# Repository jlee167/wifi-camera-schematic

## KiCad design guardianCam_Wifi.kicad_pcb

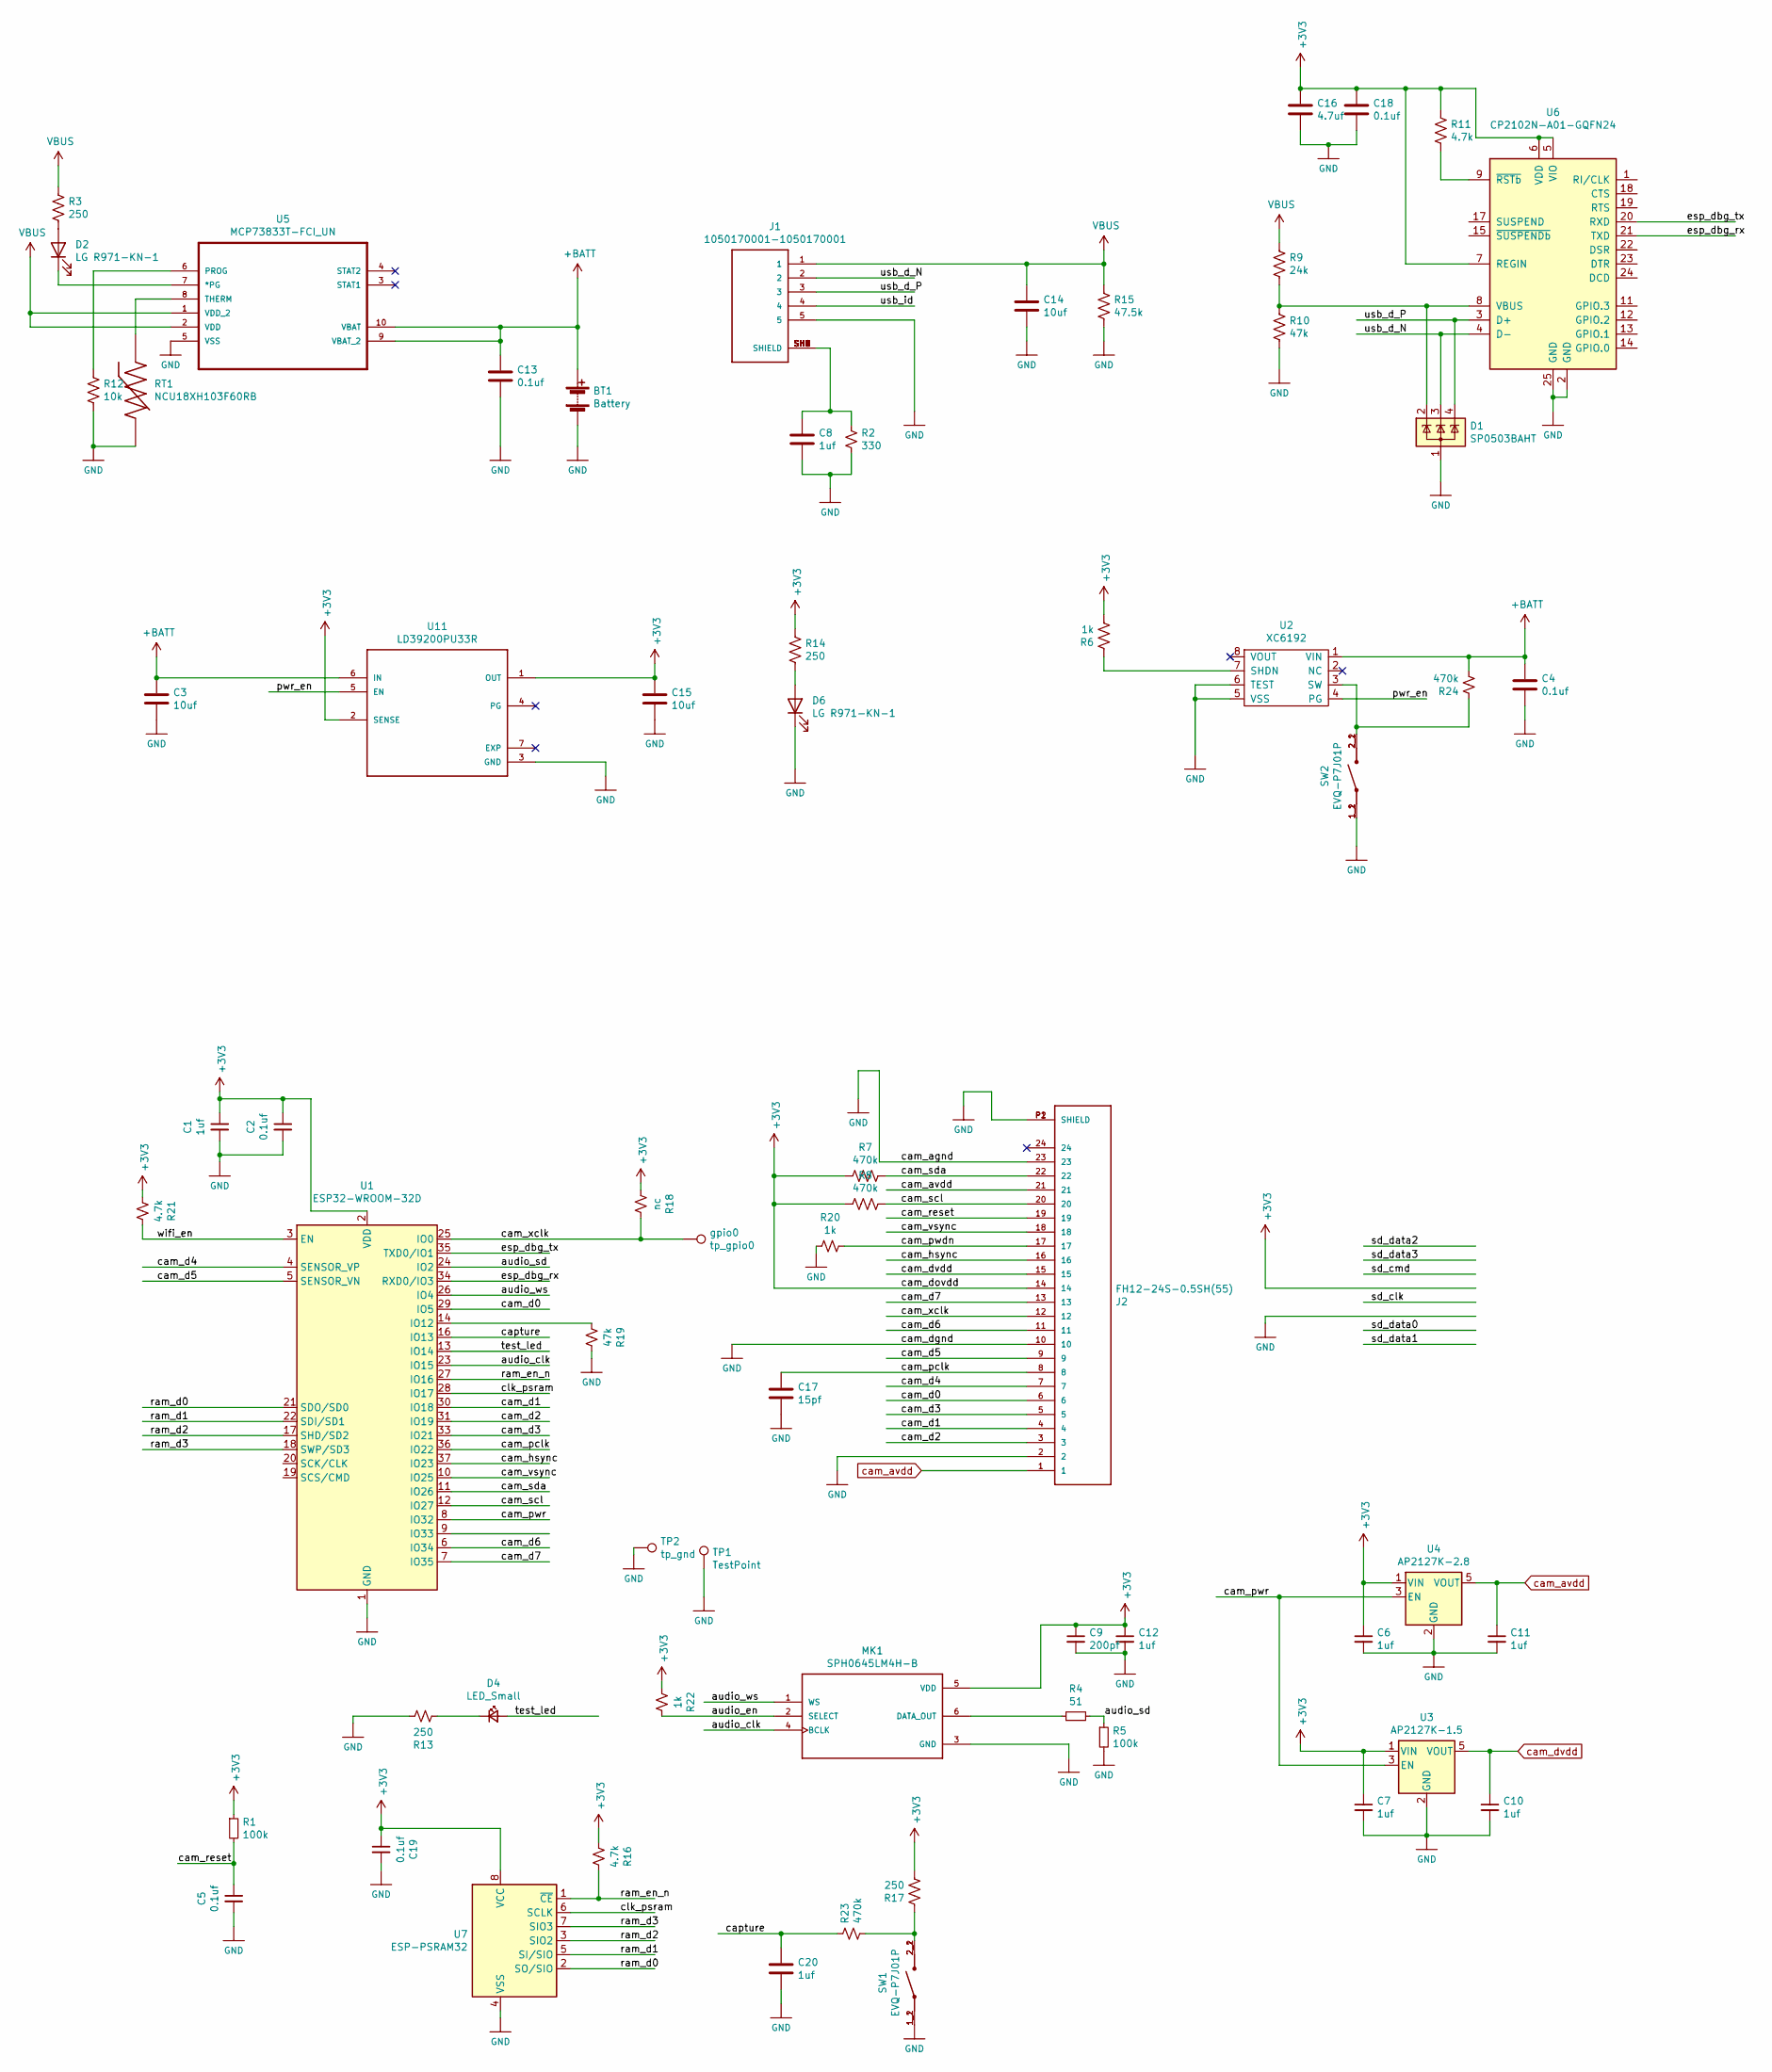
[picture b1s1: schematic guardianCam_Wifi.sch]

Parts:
BT1: Battery; JST_PH_S2B-PH-K_1x02_P2.00mm_Horizontal
C1, C6, C7, C8, C10, C11, C12, C20: 1uf; C_0603_1608Metric_Pad1.05x0.95mm_HandSolder
C2, C4, C5, C13, C18, C19: 0.1uf; C_0603_1608Metric_Pad1.05x0.95mm_HandSolder
C3, C14, C15: 10uf; C_0603_1608Metric_Pad1.05x0.95mm_HandSolder
C9: 200pf; C_0603_1608Metric_Pad1.05x0.95mm_HandSolder
C16: 4.7uf; C_0603_1608Metric_Pad1.05x0.95mm_HandSolder
C17: 15pf; C_0603_1608Metric_Pad1.05x0.95mm_HandSolder
D1: SP0503BAHT; SOT-143
D2, D6: LG R971-KN-1; LED_1206_3216Metric
D4: LED_Small; LED_1206_3216Metric
J1: 1050170001-1050170001; MOLEX_1050170001
J2: FH12-24S-0.5SH(55); HRS_FH12-24S-0.5SH(55)
MK1: SPH0645LM4H-B; MIC_SPH0645LM4H-B
R1, R5: 100k; R_0603_1608Metric_Pad1.05x0.95mm_HandSolder
R2: 330; R_0603_1608Metric_Pad1.05x0.95mm_HandSolder
R3, R13, R14, R17: 250; R_0603_1608Metric_Pad1.05x0.95mm_HandSolder
R4: 51; R_0603_1608Metric_Pad1.05x0.95mm_HandSolder
R6, R20, R22: 1k; R_0603_1608Metric_Pad1.05x0.95mm_HandSolder
R7, R8, R23, R24: 470k; R_0603_1608Metric_Pad1.05x0.95mm_HandSolder
R9: 24k; R_0603_1608Metric_Pad1.05x0.95mm_HandSolder
R10, R19: 47k; R_0603_1608Metric_Pad1.05x0.95mm_HandSolder
R11, R16, R21: 4.7k; R_0603_1608Metric_Pad1.05x0.95mm_HandSolder
R12: 10k; R_0603_1608Metric_Pad1.05x0.95mm_HandSolder
R15: 47.5k; R_0603_1608Metric_Pad1.05x0.95mm_HandSolder
R18: nc; R_0603_1608Metric_Pad1.05x0.95mm_HandSolder
RT1: NCU18XH103F60RB
SW1, SW2: EVQ-P7J01P
TP1: TestPoint; TestPoint_THTPad_D3.0mm_Drill1.5mm
TP2: tp_gnd; TestPoint_THTPad_D1.5mm_Drill0.7mm
U1: ESP32-WROOM-32D; ESP32-WROOM-32
U2: XC6192; xc6192
U3: AP2127K-1.5; SOT-23-5
U4: AP2127K-2.8; SOT-23-5
U5: MCP73833T-FCI_UN
U6: CP2102N-A01-GQFN24; QFN-24-1EP_4x4mm_P0.5mm_EP2.6x2.6mm
U7: ESP-PSRAM32; SOIC-8_3.9x4.9mm_P1.27mm
U11: LD39200PU33R
gpio0: tp_gpio0; TestPoint_THTPad_D1.5mm_Drill0.7mm

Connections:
+3V3: C1.1, C2.1, C6.1, C7.1, C9.1, C12.1, C15.1, C16.1, C18.1, C19.1, J2.14, MK1.5 (VDD), R1.1, R6.2, R7.2, R8.2, R11.1, R14.1, R16.2, R17.2, R18.2, R21.2, R22.2, U1.2 (VDD), U3.1 (VIN), U4.1 (VIN), U6.5 (VIO), U6.6 (VDD), U6.7 (REGIN), U7.8 (VCC), U11.1 (OUT), U11.2 (SENSE)
+BATT: BT1.1 (+), C3.1, C4.1, C13.1, R24.2, U2.1 (VIN), U5.9 (VBAT_2), U5.10 (VBAT), U11.6 (IN)
/audio_clk: MK1.4 (BCLK), U1.23 (IO15)
/audio_en: MK1.2 (SELECT), R22.1
/audio_sd: R4.2, R5.1, U1.24 (IO2)
/audio_ws: MK1.1 (WS), U1.26 (IO4)
/cam_d0: J2.6, U1.29 (IO5)
/cam_d1: J2.4, U1.30 (IO18)
/cam_d2: J2.3, U1.31 (IO19)
/cam_d3: J2.5, U1.33 (IO21)
/cam_d4: J2.7, U1.4 (SENSOR_VP)
/cam_d5: J2.9, U1.5 (SENSOR_VN)
/cam_d6: J2.11, U1.6 (IO34)
/cam_d7: J2.13, U1.7 (IO35)
/cam_hsync: J2.16, U1.37 (IO23)
/cam_pclk: C17.1, J2.8, U1.36 (IO22)
/cam_pwdn: J2.17, R20.1
/cam_pwr: U1.8 (IO32), U3.3 (EN), U4.3 (EN)
/cam_reset: C5.1, J2.19, R1.2
/cam_scl: J2.20, R8.1, U1.12 (IO27)
/cam_sda: J2.22, R7.1, U1.11 (IO26)
/cam_vsync: J2.18, U1.10 (IO25)
/cam_xclk: J2.12, R18.1, U1.25 (IO0), gpio0.1
/capture: C20.1, R23.1, U1.16 (IO13)
/clk_psram: U1.28 (IO17), U7.6 (SCLK)
/esp_dbg_rx: U1.34 (RXD0/IO3), U6.21 (TXD)
/esp_dbg_tx: U1.35 (TXD0/IO1), U6.20 (RXD)
/pwr_en: U2.4 (PG), U11.5 (EN)
/ram_d0: U1.21 (SDO/SD0), U7.2 (SO/SIO)
/ram_d1: U1.22 (SDI/SD1), U7.5 (SI/SIO)
/ram_d2: U1.17 (SHD/SD2), U7.3 (SIO2)
/ram_d3: U1.18 (SWP/SD3), U7.7 (SIO3)
/ram_en_n: R16.1, U1.27 (IO16), U7.1 (~CE)
/test_led: D4.2 (A), U1.13 (IO14)
/usb_d_N: D1.3 (K), J1.2, U6.4 (D-)
/usb_d_P: D1.4 (K), J1.3, U6.3 (D+)
/wifi_en: R21.1, U1.3 (EN)
GND: BT1.2 (-), C1.2, C2.2, C3.2, C4.2, C5.2, C6.2, C7.2, C8.2, C9.2, C10.2, C11.2, C12.2, C13.2, C14.2, C15.2, C16.2, C17.2, C18.2, C19.2, C20.2, D1.1 (A), D6.1 (K), J1.5, J2.2, J2.10, J2.23, J2.P1 (SHIELD), J2.P2 (SHIELD), MK1.3 (GND), R2.2, R5.2, R10.2, R12.2, R13.1, R15.2, R19.1, R20.2, RT1.2, SW1.1_1, SW1.1_2, SW2.1_1, SW2.1_2, TP1.1, TP2.1, U1.1 (GND), U1.15 (GND), U1.38 (GND), U1.39 (GND), U2.5 (VSS), U2.6 (TEST), U3.2 (GND), U4.2 (GND), U5.5 (VSS), U6.2 (GND), U6.25 (GND), U7.4 (VSS), U11.3 (GND)
unnamed: C8.1, J1.SH1 (SHIELD), J1.SH2 (SHIELD), J1.SH3 (SHIELD), J1.SH4 (SHIELD), J1.SH5 (SHIELD), J1.SH6 (SHIELD), J1.SH7 (SHIELD), J1.SH8 (SHIELD), R2.1
unnamed: D1.2 (K), R9.2, R10.1, U6.8 (VBUS)
unnamed: D2.1 (K), U5.7 (*PG)
unnamed: D2.2 (A), R3.2
unnamed: D4.1 (K), R13.2
unnamed: D6.2 (A), R14.2
unnamed: MK1.6 (DATA_OUT), R4.1
unnamed: R6.1, U2.7 (SHDN)
unnamed: R11.2, U6.9 (~RSTb)
unnamed: R12.1, U5.6 (PROG)
unnamed: R17.1, R23.2, SW1.2_1, SW1.2_2
unnamed: R19.2, U1.14 (IO12)
unnamed: R24.1, SW2.2_1, SW2.2_2, U2.3 (SW)
unnamed: RT1.1, U5.8 (THERM)
VBUS: C14.1, J1.1, R3.1, R9.1, R15.1, U5.1 (VDD_2), U5.2 (VDD)
cam_avdd: C11.1, J2.1, J2.21, U4.5 (VOUT)
cam_dvdd: C10.1, J2.15, U3.5 (VOUT)

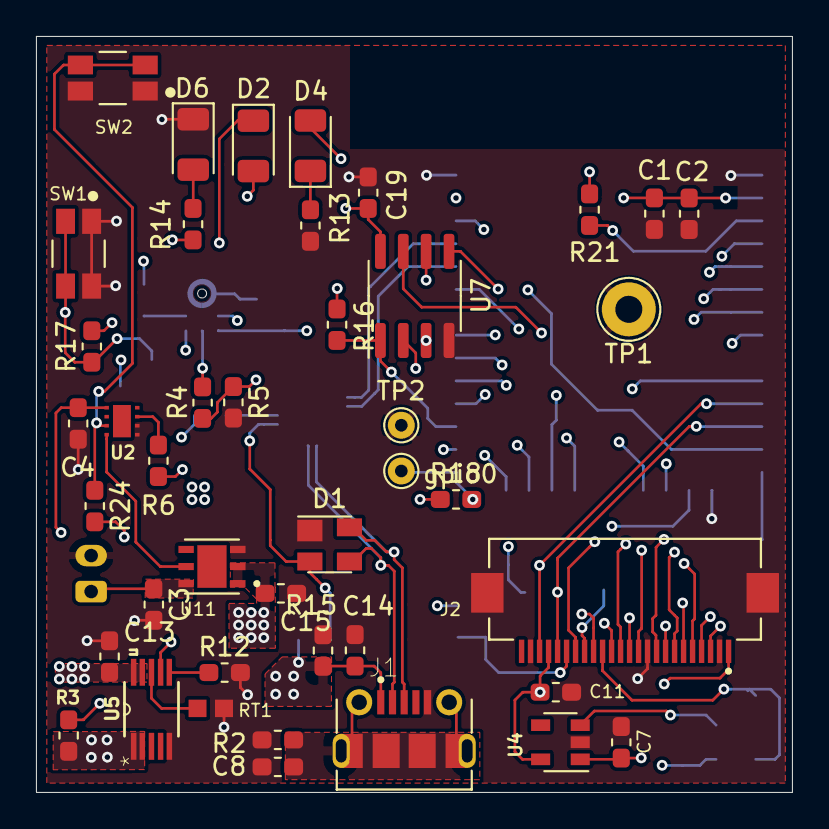
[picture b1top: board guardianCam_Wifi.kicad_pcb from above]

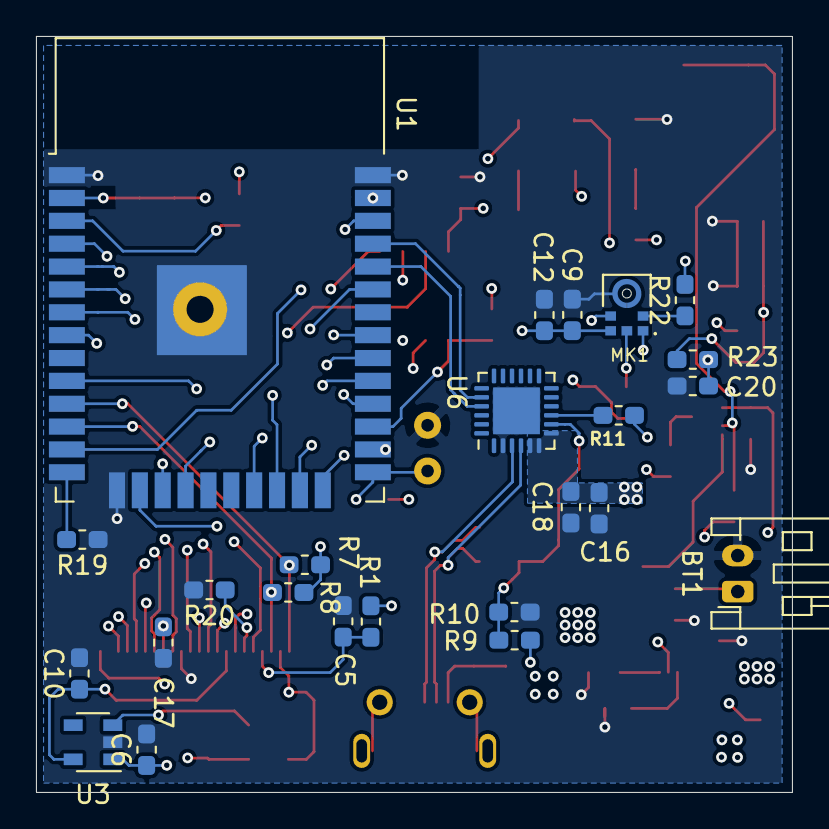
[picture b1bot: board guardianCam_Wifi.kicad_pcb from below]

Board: 4 copper layers, 42.0 x 42.0 mm, 66 parts (24 on the bottom side), 55 nets.

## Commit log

2021-04-28 base
